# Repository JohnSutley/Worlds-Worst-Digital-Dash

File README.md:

This folder contains the project files for the Worlds Worst Digital Dash
(Gameboy Digital Dash) project. If attempting to recreate version 1 of the
Arduino CANBUS card, please make a note of the included "Project Note" and 
"Project Note 2" pictures in the "Arduino Canbus Card" project folder, since 
I totally messed up the DB9 connector pinout and missed a trace leading to 
the 7805 voltage regulator. Also, I had to bridge some connections on top of 
the Arduino. Gotta admit, not my best work. The "reader.gb" file in the 
Gameboy Code folder is the pre-compiled binary that gets flashed to the EEPROM. 
The software used in this project is as follows:

-Kicad 7.0

-Autodesk Fusion 2.0.20494 x86_64

-Arduino IDE Version: 2.3.4

-GBDK-2020

-Savvy CAN V208

-Xgpro v12.66

-UltiMaker Cura 5.6.0

-LightBurn 1.6.03

-GIMP 2.10.36

-Visual Studio Code Version: 1.96.2

I think LightBurn was the only paid software I used, and that was for the
laser engraver.

Feel free to contact me with any questions regarding this project at
jcsutley@gmail.com. 

John Sutley - 2025

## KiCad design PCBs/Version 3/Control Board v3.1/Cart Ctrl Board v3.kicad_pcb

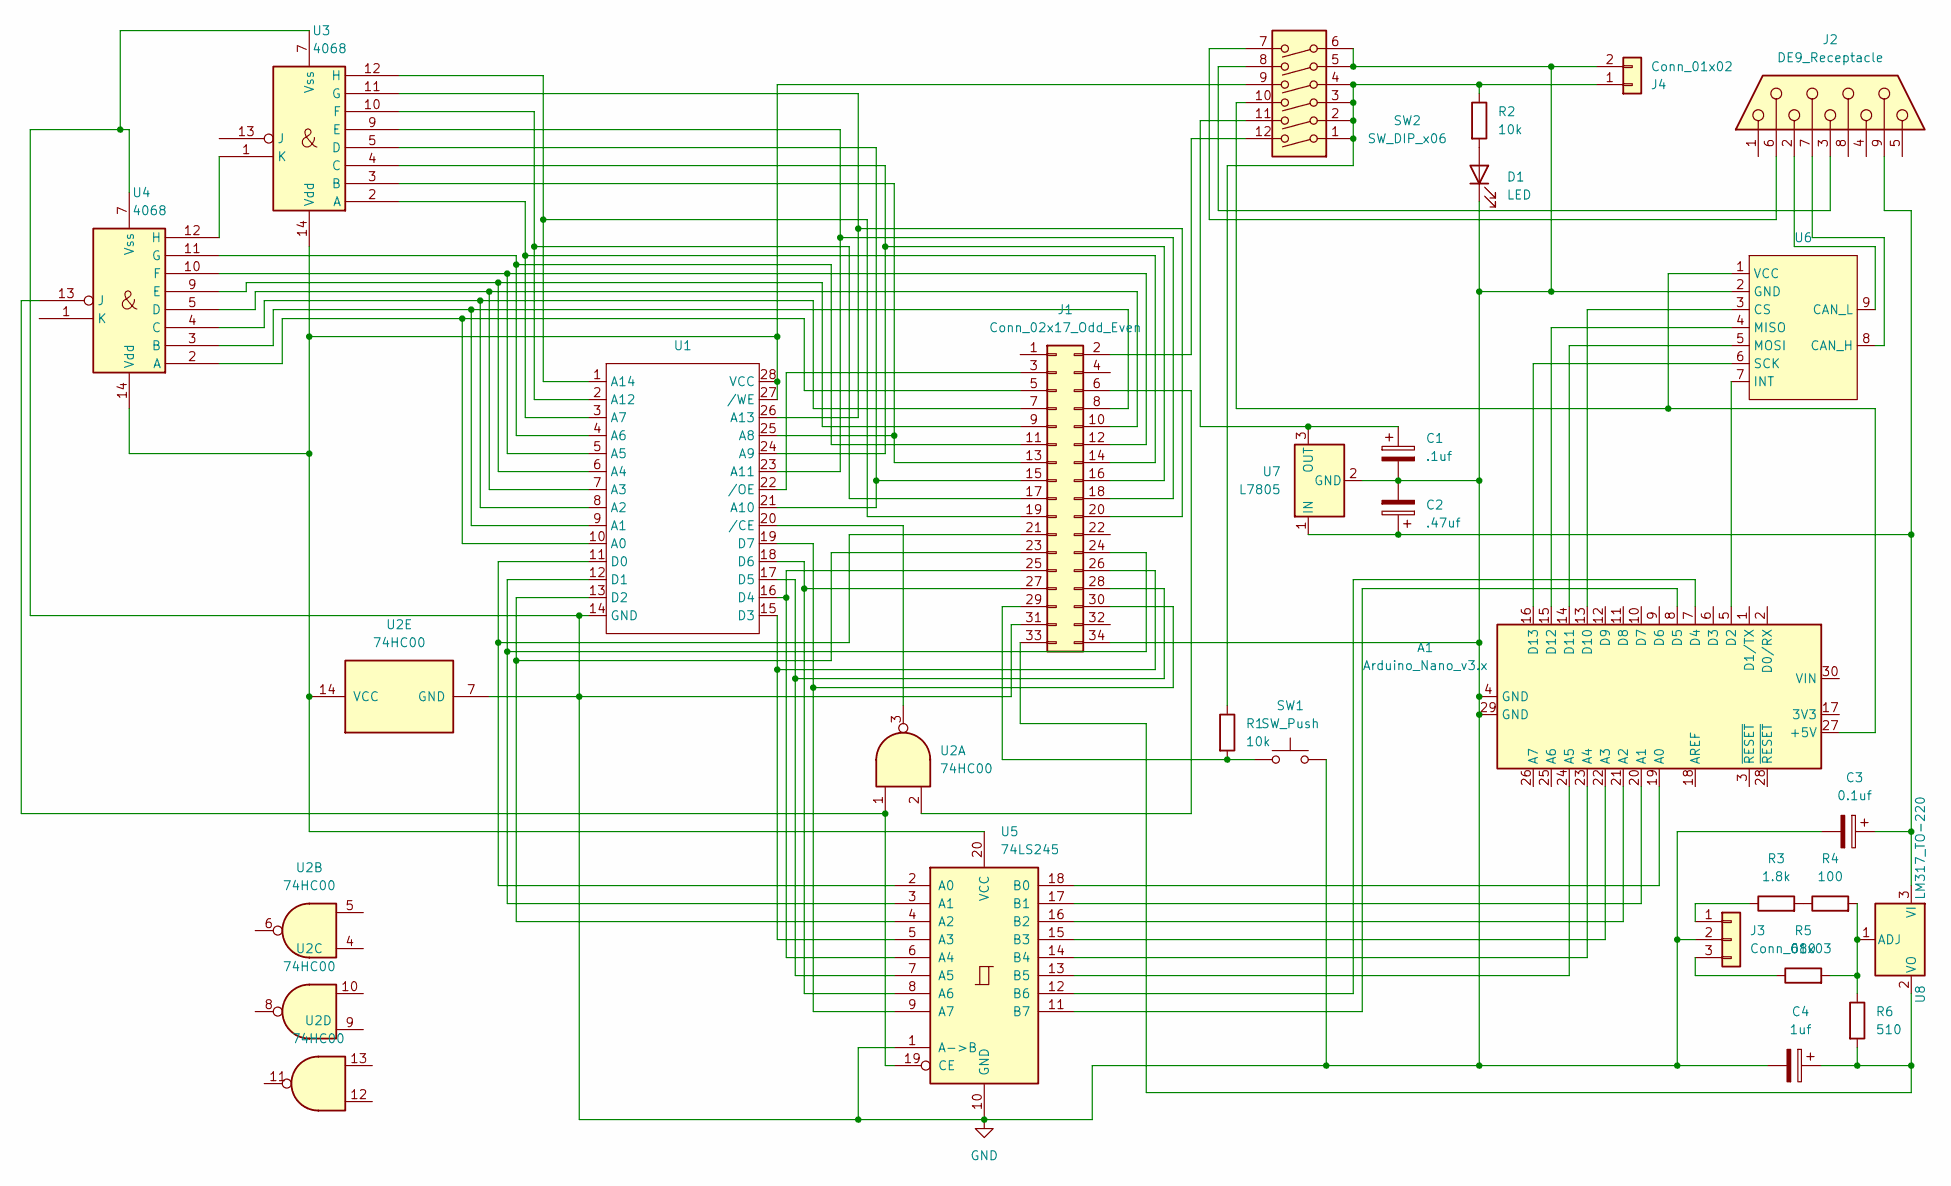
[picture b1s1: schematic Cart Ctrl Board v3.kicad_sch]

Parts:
A1: Arduino_Nano_v3.x; Arduino_Nano
C1: .1uf; CP_Radial_D4.0mm_P2.00mm
C2: .47uf; CP_Radial_D4.0mm_P2.00mm
C3: 0.1uf; CP_Radial_D4.0mm_P2.00mm
C4: 1uf; CP_Radial_D4.0mm_P2.00mm
D1: LED; LED_D5.0mm
J1: Conn_02x17_Odd_Even; PinHeader_2x17_P2.54mm_Vertical
J2: DE9_Receptacle; DSUB-9_Male_Horizontal_P2.77x2.84mm_EdgePinOffset7.70mm_Hou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
J3: Conn_01x03; PinHeader_1x03_P2.54mm_Vertical
J4: Conn_01x02; PinSocket_1x02_P2.54mm_Vertical
R1, R2: 10k; R_Axial_DIN0207_L6.3mm_D2.5mm_P7.62mm_Horizontal
R3: 1.8k; R_Axial_DIN0207_L6.3mm_D2.5mm_P7.62mm_Horizontal
R4: 100; R_Axial_DIN0207_L6.3mm_D2.5mm_P7.62mm_Horizontal
R5: 680; R_Axial_DIN0207_L6.3mm_D2.5mm_P7.62mm_Horizontal
R6: 510; R_Axial_DIN0207_L6.3mm_D2.5mm_P7.62mm_Horizontal
SW1: SW_Push; SW_PUSH_6mm
SW2: SW_DIP_x06; DIP-12_W7.62mm_LongPads
U1: DIP-28_W15.24mm_LongPads
U2: 74HC00; DIP-14_W7.62mm_LongPads
U3, U4: 4068; DIP-14_W7.62mm_LongPads
U5: 74LS245; DIP-20_W7.62mm_LongPads
U6: MCP2515_MODULE
U7: L7805; TO-220-3_Vertical
U8: LM317_TO-220; TO-220-3_Vertical

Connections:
GND: A1.4 (GND), A1.29 (GND), C1.2, C2.2, C3.2, C4.2, D1.1 (K), J1.31, J1.34, J3.2, J4.2, SW1.2, SW2.5, SW2.6, U1.14 (GND), U2.7 (GND), U3.7 (Vss), U4.7 (Vss), U5.1 (A->B), U5.10 (GND), U6.2 (GND), U7.2 (GND)
unnamed: A1.27 (+5V), SW2.10, U6.1 (VCC)
unnamed: A1.19 (A0), U5.18 (B0)
unnamed: A1.20 (A1), U5.17 (B1)
unnamed: A1.21 (A2), U5.16 (B2)
unnamed: A1.22 (A3), U5.15 (B3)
unnamed: A1.23 (A4), U5.14 (B4)
unnamed: A1.24 (A5), U5.13 (B5)
unnamed: A1.5 (D2), U6.7 (INT)
unnamed: A1.7 (D4), U5.12 (B6)
unnamed: A1.8 (D5), U5.11 (B7)
unnamed: A1.13 (D10), U6.3 (CS)
unnamed: A1.14 (D11), U6.5 (MOSI)
unnamed: A1.15 (D12), U6.4 (MISO)
unnamed: A1.16 (D13), U6.6 (SCK)
unnamed: D1.2 (A), R2.2
unnamed: J1.2, SW2.12
unnamed: J1.3, U1.22 (/OE)
unnamed: J1.5, U1.10 (A0), U4.2 (A)
unnamed: J1.6, U2.2
unnamed: J1.7, U1.8 (A2), U4.4 (C)
unnamed: J1.8, U1.9 (A1), U4.3 (B)
unnamed: J1.9, U1.6 (A4), U4.9 (E)
unnamed: J1.10, U1.7 (A3), U4.5 (D)
unnamed: J1.11, U1.4 (A6), U4.11 (G)
unnamed: J1.12, U1.5 (A5), U4.10 (F)
unnamed: J1.13, U1.25 (A8), U3.3 (B)
unnamed: J1.14, U1.3 (A7), U3.2 (A)
unnamed: J1.15, U1.21 (A10), U3.5 (D)
unnamed: J1.16, U1.24 (A9), U3.4 (C)
unnamed: J1.17, U1.2 (A12), U3.10 (F)
unnamed: J1.18, U1.23 (A11), U3.9 (E)
unnamed: J1.19, U1.1 (A14), U3.12 (H)
unnamed: J1.20, U1.26 (A13), U3.11 (G)
unnamed: J1.21, U1.11 (D0), U5.2 (A0)
unnamed: J1.23, U1.13 (D2), U5.4 (A2)
unnamed: J1.24, U1.12 (D1), U5.3 (A1)
unnamed: J1.25, U1.16 (D4), U5.6 (A4)
unnamed: J1.26, U1.15 (D3), U5.5 (A3)
unnamed: J1.27, U1.18 (D6), U5.8 (A6)
unnamed: J1.28, U1.17 (D5), U5.7 (A5)
unnamed: J1.29, R1.2, SW1.1
unnamed: J1.30, U1.19 (D7), U5.9 (A7)
unnamed: C4.1, J1.33, R6.2, U8.2 (VO)
unnamed: J2.3, SW2.8
unnamed: J2.6, SW2.7
unnamed: J3.1, R3.1
unnamed: J3.3, R5.1
unnamed: J4.1, R1.1, R2.1, SW2.1, SW2.2, SW2.3, SW2.4
unnamed: R3.2, R4.1
unnamed: SW2.9, U1.27 (/WE), U1.28 (VCC), U2.14 (VCC), U3.14 (Vdd), U4.14 (Vdd), U5.20 (VCC)
unnamed: U1.20 (/CE), U2.3
unnamed: U3.1 (K), U4.12 (H)
unnamed: U2.1, U4.13 (J), U5.19 (CE)
unnamed: J2.7, U6.8 (CAN_H)
unnamed: J2.2, U6.9 (CAN_L)
unnamed: C2.1, C3.1, J2.9, U7.1 (IN), U8.3 (VI)
unnamed: C1.1, SW2.11, U7.3 (OUT)
unnamed: R4.2, R5.2, R6.1, U8.1 (ADJ)

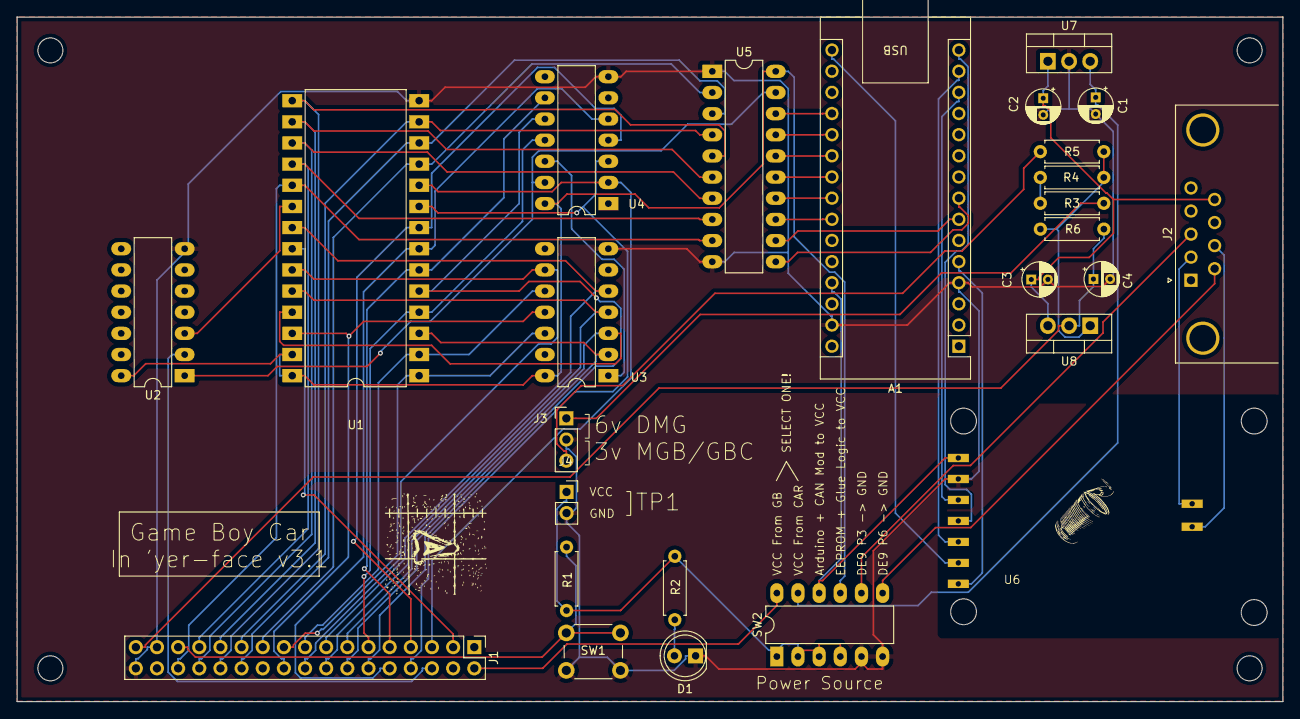
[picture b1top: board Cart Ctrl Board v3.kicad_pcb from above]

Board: 2 copper layers, 152.0 x 82.2 mm, 26 parts (0 on the bottom side), 59 nets.

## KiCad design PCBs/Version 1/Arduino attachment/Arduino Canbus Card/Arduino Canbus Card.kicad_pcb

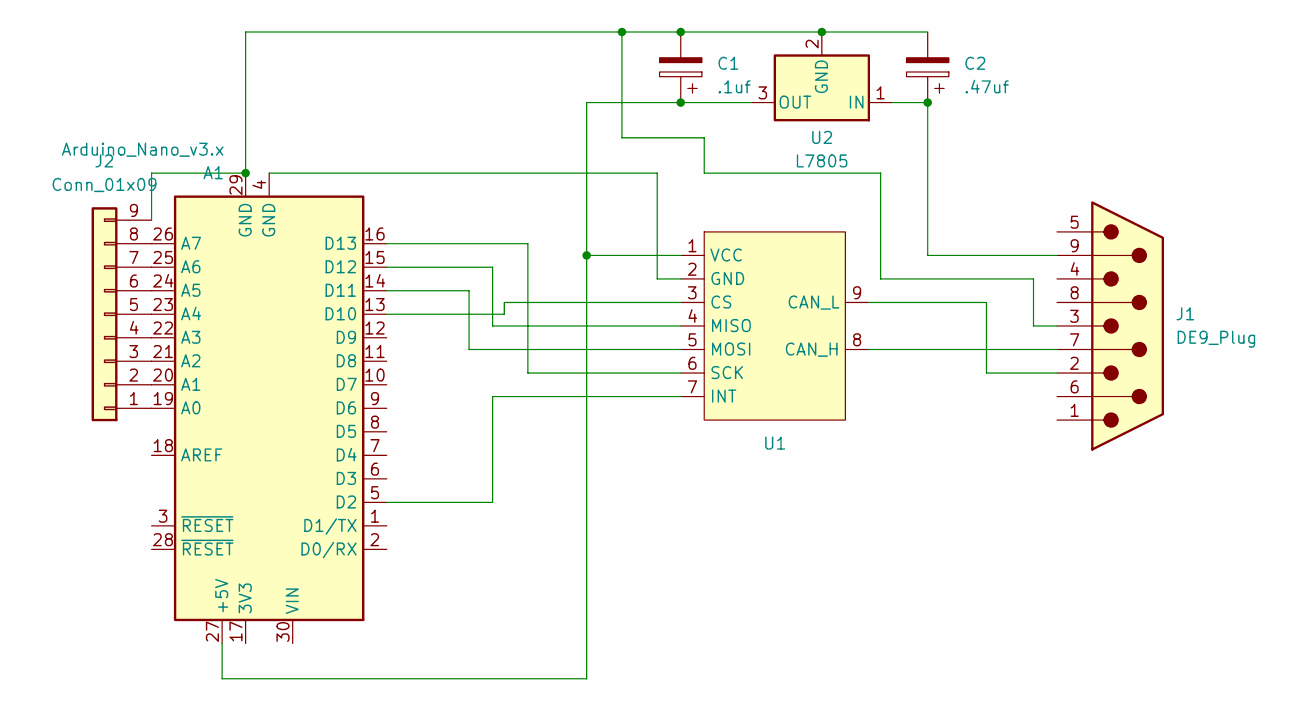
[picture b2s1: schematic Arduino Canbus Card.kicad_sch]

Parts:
A1: Arduino_Nano_v3.x; Arduino_Nano
C1: .1uf; CP_Radial_D5.0mm_P2.50mm
C2: .47uf; CP_Radial_D5.0mm_P2.50mm
J1: DE9_Plug; DSUB-9_Female_Horizontal_P2.77x2.84mm_EdgePinOffset4.94mm_H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
J2: Conn_01x09; PinSocket_1x09_P2.54mm_Horizontal
U1: MCP2515_MODULE
U2: L7805; TO-220-3_Vertical

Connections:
unnamed: A1.27 (+5V), C1.1, U1.1 (VCC), U2.3 (OUT)
unnamed: A1.19 (A0), J2.1
unnamed: A1.20 (A1), J2.2
unnamed: A1.21 (A2), J2.3
unnamed: A1.22 (A3), J2.4
unnamed: A1.23 (A4), J2.5
unnamed: A1.24 (A5), J2.6
unnamed: A1.25 (A6), J2.7
unnamed: A1.26 (A7), J2.8
unnamed: A1.5 (D2), U1.7 (INT)
unnamed: A1.13 (D10), U1.3 (CS)
unnamed: A1.14 (D11), U1.5 (MOSI)
unnamed: A1.15 (D12), U1.4 (MISO)
unnamed: A1.16 (D13), U1.6 (SCK)
unnamed: A1.29 (GND), C1.2, C2.2, J1.3, J2.9, U2.2 (GND)
unnamed: J1.7, U1.8 (CAN_H)
unnamed: J1.2, U1.9 (CAN_L)
unnamed: A1.4 (GND), U1.2 (GND)
unnamed: C2.1, J1.9, U2.1 (IN)

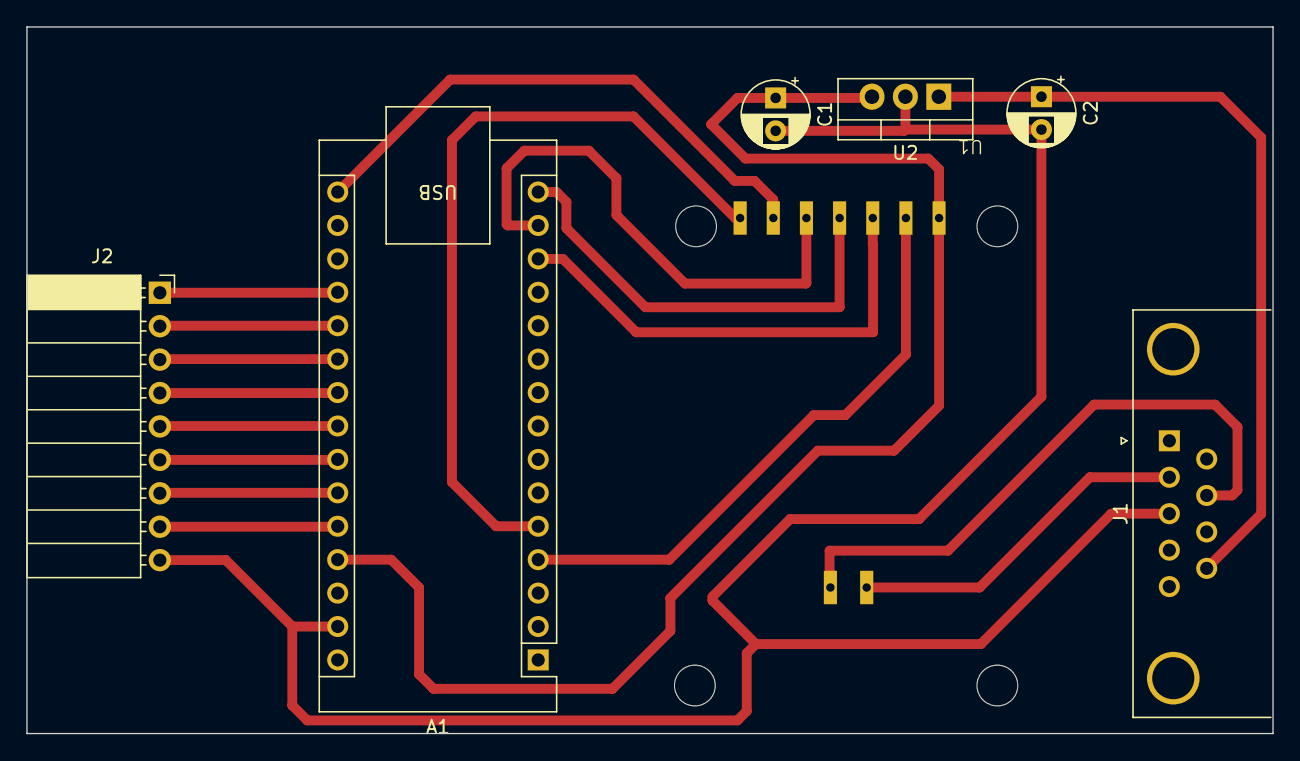
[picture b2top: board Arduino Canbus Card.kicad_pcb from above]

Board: 2 copper layers, 94.7 x 53.7 mm, 7 parts (0 on the bottom side), 19 nets.

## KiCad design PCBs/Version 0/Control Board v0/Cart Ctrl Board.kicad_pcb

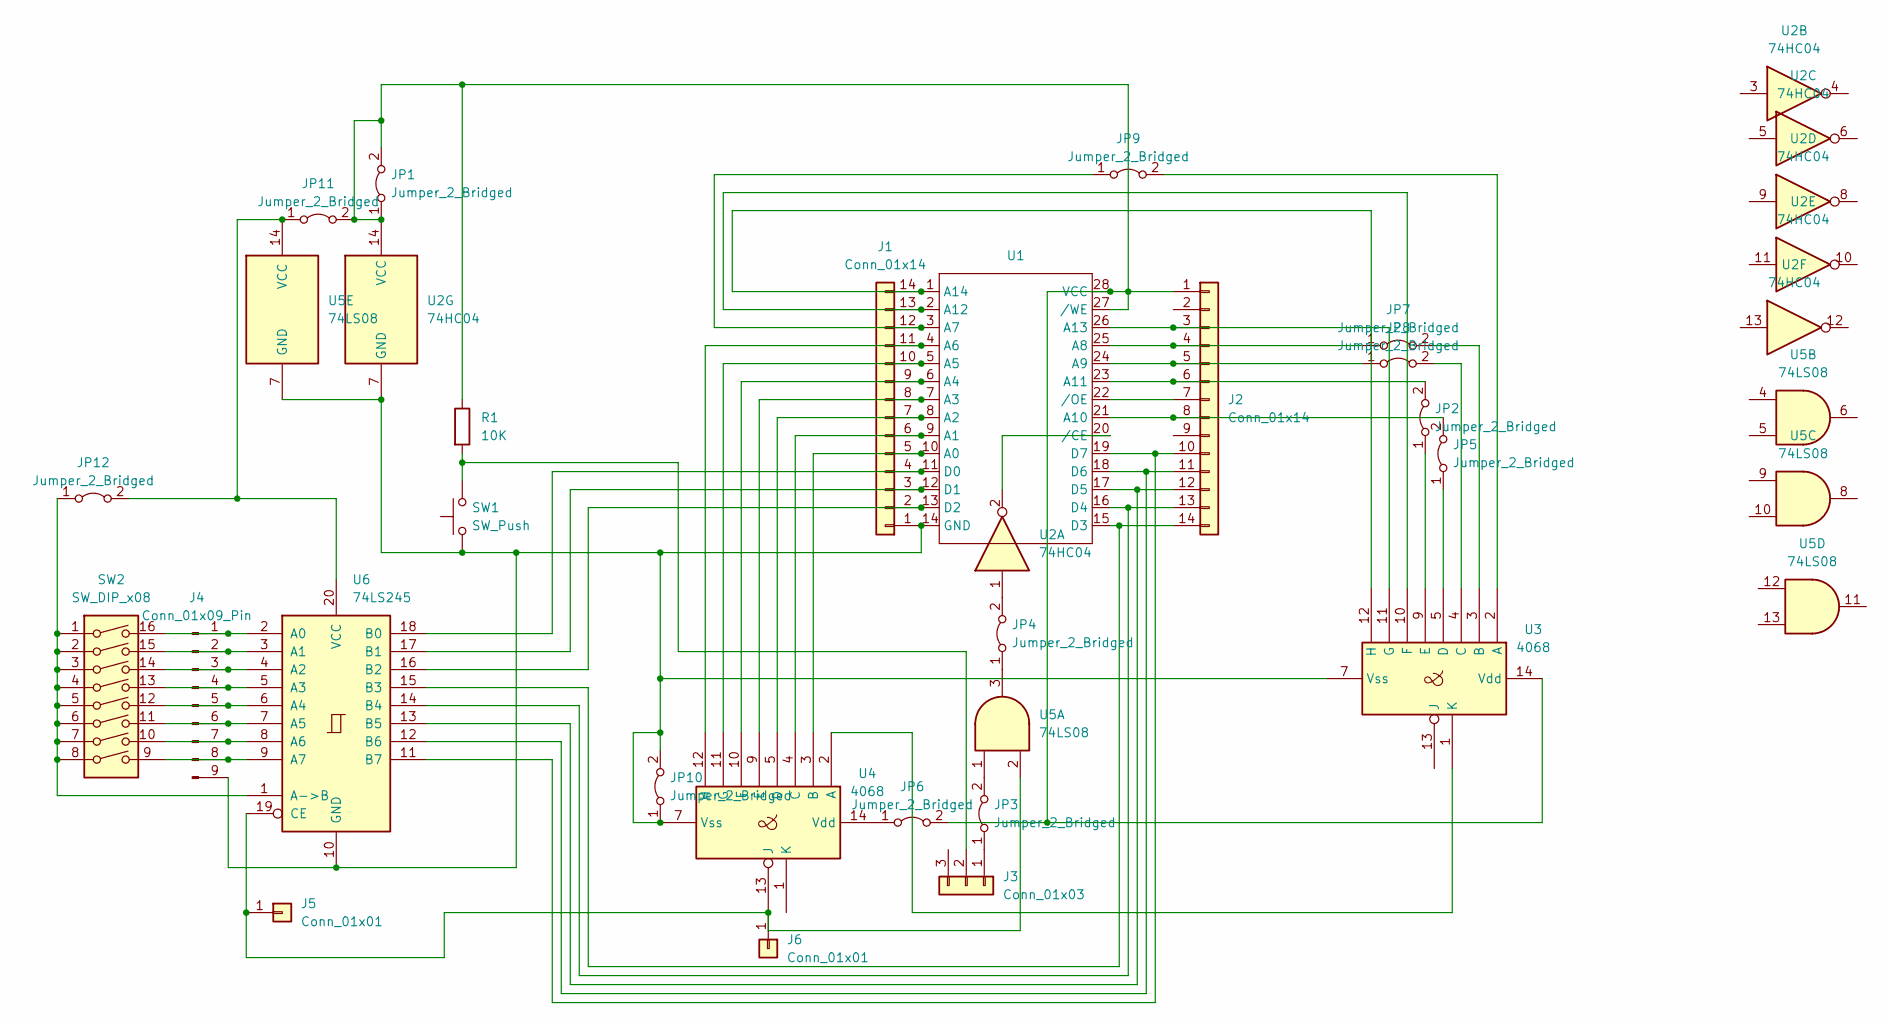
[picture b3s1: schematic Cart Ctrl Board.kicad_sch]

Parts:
J1, J2: Conn_01x14; PinHeader_1x14_P2.54mm_Vertical
J3: Conn_01x03; PinHeader_1x03_P2.54mm_Vertical
J4: Conn_01x09_Pin; SIP-9_22.3x3mm_P2.54mm
J5, J6: Conn_01x01; PinHeader_1x01_P2.54mm_Vertical
JP1, JP2, JP3, JP4, JP5, JP6, JP7, JP9, JP11: Jumper_2_Bridged; R_Axial_DIN0207_L6.3mm_D2.5mm_P10.16mm_Horizontal
JP8, JP10: Jumper_2_Bridged; R_Axial_DIN0207_L6.3mm_D2.5mm_P15.24mm_Horizontal
JP12: Jumper_2_Bridged; R_Axial_DIN0207_L6.3mm_D2.5mm_P7.62mm_Horizontal
R1: 10K; R_Axial_DIN0207_L6.3mm_D2.5mm_P10.16mm_Horizontal
SW1: SW_Push; SW_PUSH_6mm_H5mm
SW2: SW_DIP_x08; DIP-16_W7.62mm_LongPads
U1: DIP-28_W15.24mm_LongPads
U2: 74HC04; DIP-14_W7.62mm_LongPads
U3, U4: 4068; DIP-14_W7.62mm_LongPads
U5: 74LS08; DIP-14_W7.62mm_LongPads
U6: 74LS245; DIP-20_W7.62mm_LongPads

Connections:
unnamed: J1.1, J4.9, JP10.1 (A), JP10.2 (B), SW1.1, U1.14 (GND), U2.7 (GND), U3.7 (Vss), U4.7 (Vss), U5.7 (GND), U6.10 (GND)
unnamed: J1.2, U1.13 (D2), U6.16 (B2)
unnamed: J1.3, U1.12 (D1), U6.17 (B1)
unnamed: J1.4, U1.11 (D0), U6.18 (B0)
unnamed: J1.5, U1.10 (A0), U4.3 (B)
unnamed: J1.6, U1.9 (A1), U4.4 (C)
unnamed: J1.7, U1.8 (A2), U4.5 (D)
unnamed: J1.8, U1.7 (A3), U4.9 (E)
unnamed: J1.9, U1.6 (A4), U4.10 (F)
unnamed: J1.10, U1.5 (A5), U4.11 (G)
unnamed: J1.11, U1.4 (A6), U4.12 (H)
unnamed: J1.12, JP9.1 (A), U1.3 (A7)
unnamed: J1.13, U1.2 (A12), U3.10 (F)
unnamed: J1.14, U1.1 (A14), U3.12 (H)
unnamed: J2.1, JP1.1 (A), JP1.2 (B), JP6.2 (B), JP11.2 (B), R1.1, U1.27 (/WE), U1.28 (VCC), U2.14 (VCC), U3.14 (Vdd)
unnamed: J2.3, U1.26 (A13), U3.11 (G)
unnamed: J2.4, JP7.1 (A), U1.25 (A8)
unnamed: J2.5, JP8.1 (A), U1.24 (A9)
unnamed: J2.6, JP2.2 (B), U1.23 (A11)
unnamed: J2.7, U1.22 (/OE)
unnamed: J2.8, JP5.2 (B), U1.21 (A10)
unnamed: J2.10, U1.19 (D7), U6.11 (B7)
unnamed: J2.11, U1.18 (D6), U6.12 (B6)
unnamed: J2.12, U1.17 (D5), U6.13 (B5)
unnamed: J2.13, U1.16 (D4), U6.14 (B4)
unnamed: J2.14, U1.15 (D3), U6.15 (B3)
unnamed: J3.1, JP3.1 (A)
unnamed: J3.2, R1.2, SW1.2
unnamed: J4.1, SW2.16, U6.2 (A0)
unnamed: J4.2, SW2.15, U6.3 (A1)
unnamed: J4.3, SW2.14, U6.4 (A2)
unnamed: J4.4, SW2.13, U6.5 (A3)
unnamed: J4.5, SW2.12, U6.6 (A4)
unnamed: J4.6, SW2.11, U6.7 (A5)
unnamed: J4.7, SW2.10, U6.8 (A6)
unnamed: J4.8, SW2.9, U6.9 (A7)
unnamed: J5.1, J6.1, U4.13 (J), U5.2, U6.19 (CE)
unnamed: JP2.1 (A), U3.9 (E)
unnamed: JP3.2 (B), U5.1
unnamed: JP4.1 (A), U5.3
unnamed: JP4.2 (B), U2.1
unnamed: JP5.1 (A), U3.5 (D)
unnamed: JP6.1 (A), U4.14 (Vdd)
unnamed: JP7.2 (B), U3.3 (B)
unnamed: JP8.2 (B), U3.4 (C)
unnamed: JP9.2 (B), U3.2 (A)
unnamed: JP11.1 (A), JP12.2 (B), U5.14 (VCC), U6.20 (VCC)
unnamed: JP12.1 (A), SW2.1, SW2.2, SW2.3, SW2.4, SW2.5, SW2.6, SW2.7, SW2.8, U6.1 (A->B)
unnamed: U1.20 (/CE), U2.2
unnamed: U3.1 (K), U4.2 (A)

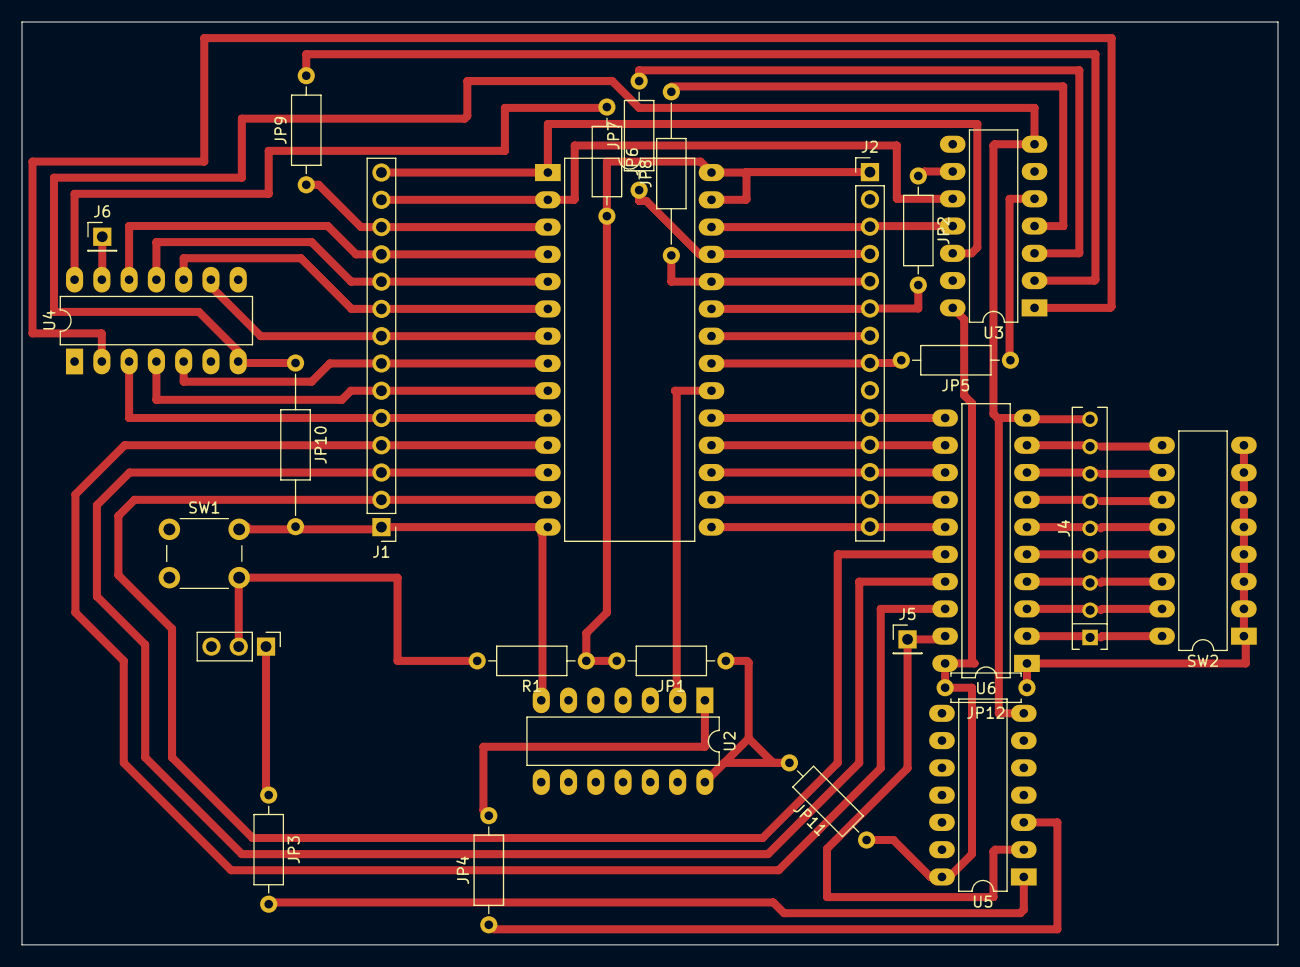
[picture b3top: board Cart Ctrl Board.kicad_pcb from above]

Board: 2 copper layers, 117.0 x 85.9 mm, 27 parts (0 on the bottom side), 50 nets.

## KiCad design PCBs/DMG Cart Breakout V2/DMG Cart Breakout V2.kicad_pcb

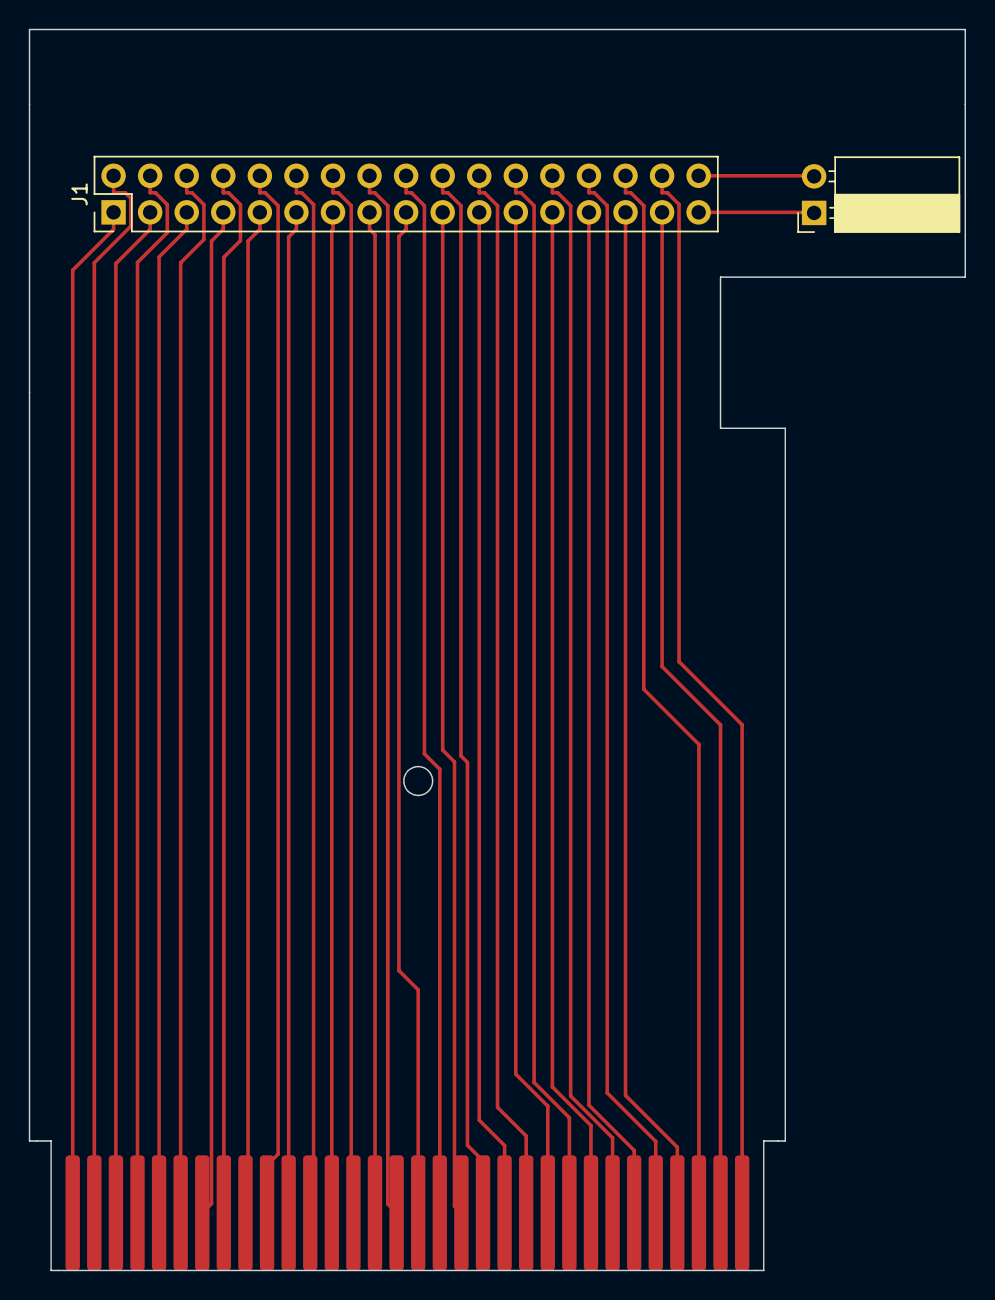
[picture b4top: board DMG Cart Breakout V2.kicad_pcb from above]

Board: 2 copper layers, 65.0 x 86.2 mm, 3 parts (0 on the bottom side), 34 nets.

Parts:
CONN1: DMG_Cart
J1: Conn_02x17_Counter_Clockwise; PinHeader_2x17_P2.54mm_Vertical
PWR: Conn_01x02; PinSocket_1x02_P2.54mm_Horizontal

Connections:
GND: CONN1.32 (GND), J1.32
unnamed: CONN1.5 (!CS_RAM), J1.5
unnamed: CONN1.4 (!RD), J1.4
unnamed: CONN1.30 (!Reset), J1.30
unnamed: CONN1.3 (!WR), J1.3
unnamed: CONN1.1 (+5), J1.1
unnamed: CONN1.6 (A0), J1.6
unnamed: CONN1.7 (A1), J1.7
unnamed: CONN1.8 (A2), J1.8
unnamed: CONN1.9 (A3), J1.9
unnamed: CONN1.10 (A4), J1.10
unnamed: CONN1.11 (A5), J1.11
unnamed: CONN1.12 (A6), J1.12
unnamed: CONN1.13 (A7), J1.13
unnamed: CONN1.14 (A8), J1.14
unnamed: CONN1.15 (A9), J1.15
unnamed: CONN1.16 (A10), J1.16
unnamed: CONN1.17 (A11), J1.17
unnamed: CONN1.18 (A12), J1.18
unnamed: CONN1.19 (A13), J1.19
unnamed: CONN1.20 (A14), J1.20
unnamed: CONN1.21 (A15), J1.21
unnamed: CONN1.31 (Audio_In), J1.31
unnamed: CONN1.2 (CLK), J1.2
unnamed: CONN1.22 (D0), J1.22
unnamed: CONN1.23 (D1), J1.23
unnamed: CONN1.24 (D2), J1.24
unnamed: CONN1.25 (D3), J1.25
unnamed: CONN1.26 (D4), J1.26
unnamed: CONN1.27 (D5), J1.27
unnamed: CONN1.28 (D6), J1.28
unnamed: CONN1.29 (D7), J1.29
unnamed: J1.33, PWR.1
unnamed: J1.34, PWR.2

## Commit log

2025-01-04 Add files via upload
    This is the binary that is flashed onto the EEPROM
